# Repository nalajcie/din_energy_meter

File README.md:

# DIN Energy Meter

**this is Work In Progress, not yet stable HW/SW**

DIN Energy Meter fitting 2-unit enclosure. Features
 - 6-circuit 3-phase 
 - CT-based (external current transformers needed)
 - ESP32 as a main MCU (WiFi)
 - ATM90E32 x2 as a metering IC
 - optional display + buttons

# Hardware

TODO: 3D model of full device

For details see [Hardware README](hardware/README.md)

# Current status

## Hardware

   - **Power board** - v0.4 prototype (not assembled)
   - **Metering board** - v0.4 prototype (assembled, in test)
   - **MCU board** - breadboard prototyping

## Software
   - basic **Metering board** test with Arduino framework done

# Inspiration

This project is heavily inspired by previous work, mainly:
 - [DIN_Rail_EnergyMonitor](https://github.com/whatnick/DIN_Rail_EnergyMonitor/) by [@whatnick](https://github.com/whatnick)
 - [Expandable 6 Channel ESP32 Energy Meter](https://github.com/CircuitSetup/Expandable-6-Channel-ESP32-Energy-Meter) by [CircuitSetup](https://github.com/CircuitSetup)

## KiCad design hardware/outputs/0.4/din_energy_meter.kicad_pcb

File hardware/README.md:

# Kicad project of DIN Energy Meter

TODO: describe how to import into clean KiCad

Done in KiCad 7.0, multi-board design in hierarchical sheet. Splitting to multiple boards is done by kikit (see `split_boards.sh` for details).

# Power Board

 - Single-phase 230V AC to 3v3 DC
 - isolated 3v3 to 3v3 for power separation between ADCs and MCU
 - fliters and burden resistors for CT input
 - 2x10 2.54mm GPIO header for connecting with the **Metering Board**

# Metering Board

 - 2x ATM90E32 for energy measurement
 - CF1/2 on GPIO headers for accuracy measurement (CF3/4 on testpoints)
 - Power Manager selectors on solder jumpers
 - isolated SPI for MCU connection
 - 2x10 2.54mm GPIO header for connecting with the **Power Board**
 - 1x10 2.54mm GPIO header for connection with the **MCU board**

# MCU Board

TODO

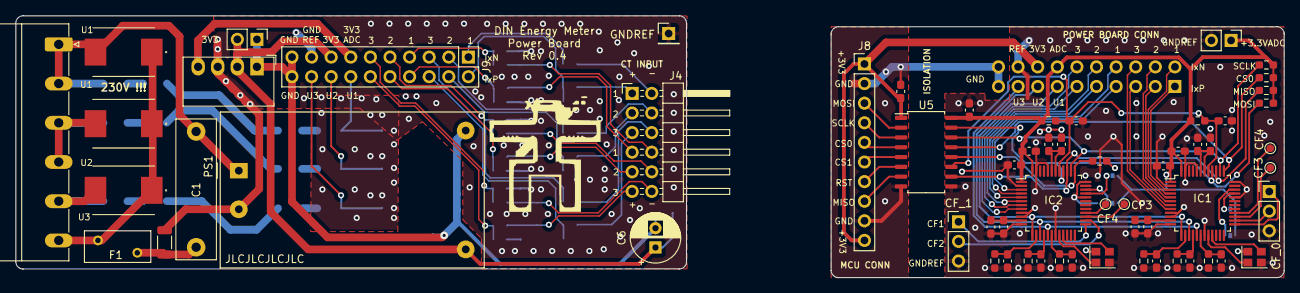
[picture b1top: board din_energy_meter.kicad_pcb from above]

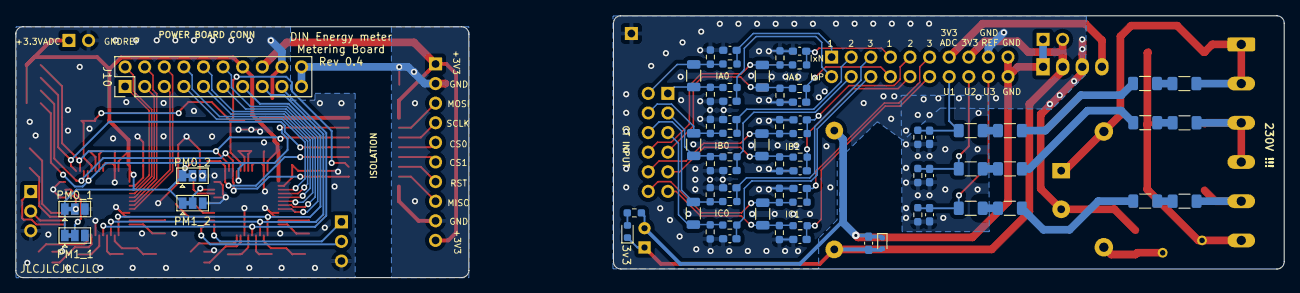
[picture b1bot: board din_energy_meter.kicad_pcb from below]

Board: 2 copper layers, 164.3 x 33.9 mm, 134 parts (69 on the bottom side), 99 nets.

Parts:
B1: PowerBoard; Board
B2: MeteringBoard; Board
C1: X2 100nF/275Vac; C_Rect_L18.0mm_W5.0mm_P15.00mm_FKS3_FKP3
C2: 1uF; C_0603_1608Metric_Pad1.08x0.95mm_HandSolder
C3, C4, C5, C10, C12, C15, C26, C28, C31, C39, C40, C41, C42, C43, C44, C45, C46, C47, C48, C49, C50: 18nF; C_0603_1608Metric_Pad1.08x0.95mm_HandSolder
C6: 100uF; CP_Radial_D6.3mm_P2.50mm
C7, C23: 4.7uF; C_0603_1608Metric_Pad1.08x0.95mm_HandSolder
C8, C9, C11, C14, C16, C17, C18, C24, C25, C27, C30, C32: 100nF; C_0603_1608Metric_Pad1.08x0.95mm_HandSolder
C13, C29: 10uF; C_0603_1608Metric_Pad1.08x0.95mm_HandSolder
D1: D_TVS; D_SOD-523
D2: 3v3; D_0603_1608Metric
F1: 120mA polyfuse; Fuse_BelFuse_0ZRE0012FF_L8.3mm_W3.8mm
G1: darwiniajack
IC1, IC2: ATM90E32AS; TQFP-48_7x7mm_P0.5mm
J1: PWR; PinHeader_1x02_P2.54mm_Vertical
J2: PHASE_CONN; PhoenixContact_MC_1,5_6-G-5.08_1x06_P5.08mm_Horizontal
J3: GNDREF; PinHeader_1x01_P2.54mm_Vertical
J4: Conn_02x06_Odd_Even; PinHeader_2x06_P2.54mm_Horizontal
J7, J11: CF_${IC}; PinHeader_1x03_P2.54mm_Vertical
J8: MCU_CONN; PinHeader_1x10_P2.54mm_Vertical
J9, J10: PowerBoard; PinHeader_2x10_P2.54mm_Vertical
J12: Conn_01x02; PinHeader_1x02_P2.54mm_Vertical
L1: 270 nH; L_1206_3216Metric
PM0_1, PM0_2, PM1_1, PM1_2: SolderJumper_3_Bridged12; SolderJumper-3_P1.3mm_Bridged12_Pad1.0x1.5mm
PS1: HLK-PM03; Converter_ACDC_HiLink_HLK-PMxx
PS2: AM1SS-0303S; Converter_DCDC_SIP4_THT
R1, R2, R3, R4, R5, R6, R7, R8, R9, R10, R11, R12: 220K; R_1206_3216Metric_Pad1.30x1.75mm_HandSolder
R13, R14, R15, R16, R17, R18, R34, R35, R36, R72, R73, R74, R75, R76, R77, R87, R88, R89, R90, R91, R92: 1K; R_0603_1608Metric_Pad0.98x0.95mm_HandSolder
R19, R37, R52, R53, R54, R55, R56: 10K; R_0603_1608Metric_Pad0.98x0.95mm_HandSolder
R22: 27; R_0603_1608Metric_Pad0.98x0.95mm_HandSolder
R63, R64, R65, R78, R79, R80: 20; R_1206_3216Metric
R66, R67, R68, R69, R70, R71, R81, R82, R83, R84, R85, R86: 2.4; R_0603_1608Metric_Pad0.98x0.95mm_HandSolder
RV1, RV2, RV3: 275 VAC; CU3225
TP2, TP11: CF3; TestPoint_Pad_D1.0mm
TP6, TP15: CF4; TestPoint_Pad_D1.0mm
U5: Π161M31; SOIC-16_4.55x10.3mm_P1.27mm
Y1, Y2: 16.384MHz; Crystal_SMD_2520-4Pin_2.5x2.0mm

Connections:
+3.3VADC: C8.2, C11.2, C18.2, C24.2, C27.2, IC1.1 (AVDD), IC1.48 (DVDD), IC2.1 (AVDD), IC2.48 (DVDD), J9.13, J10.14, J12.1, PM0_1.1 (A), PM0_2.1 (A), PM1_1.1 (A), PM1_2.1 (A), PS2.4 (+Vout), R19.1, R37.1, R52.1, R53.1, R54.1, R55.1, R56.1, U5.16 (Vdd2)
+3V3: C2.1, C6.1, C17.2, D1.2 (A2), D2.1 (K), J1.2, J8.1, J8.10, J9.15, J10.16, PS1.4 (+Vout), PS2.2 (+Vin), U5.1 (Vdd1)
/I1N_0: IC1.4 (I1N), J10.2
/I1N_1: IC2.4 (I1N), J10.8
/I1P_0: IC1.3 (I1P), J10.1
/I1P_1: IC2.3 (I1P), J10.7
/I2N_0: IC1.6 (I2N), J10.4
/I2N_1: IC2.6 (I2N), J10.10
/I2P_0: IC1.5 (I2P), J10.3
/I2P_1: IC2.5 (I2P), J10.9
/I3N_0: IC1.8 (I3N), J10.6
/I3N_1: IC2.8 (I3N), J10.12
/I3P_0: IC1.7 (I3P), J10.5
/I3P_1: IC2.7 (I3P), J10.11
/MeteringConn/CS_0: IC1.37 (~CS), R53.2, U5.13 (OUTC)
/MeteringConn/CS_1: IC2.37 (~CS), R52.2, U5.12 (OUTD)
/MeteringConn/MISO: IC1.39 (SDO), IC2.39 (SDO), R56.2, U5.10 (INF)
/MeteringConn/MOSI: IC1.40 (SDI), IC2.40 (SDI), R55.2, U5.15 (OUTA)
/MeteringConn/RESET: C16.1, C32.1, IC1.41 (~RESET), IC2.41 (~RESET), R19.2, R37.2, U5.11 (OUTE)
/MeteringConn/SCLK: IC1.38 (SCLK), IC2.38 (SCLK), R54.2, U5.14 (OUTB)
/MeteringIC0/CF1: IC1.25 (CF1), J7.1
/MeteringIC0/CF2: IC1.26 (CF2), J7.2
/MeteringIC0/PM0: IC1.33 (PM0), PM0_1.2 (C)
/MeteringIC0/PM1: IC1.34 (PM1), PM1_1.2 (C)
/MeteringIC1/CF1: IC2.25 (CF1), J11.1
/MeteringIC1/CF2: IC2.26 (CF2), J11.2
/MeteringIC1/PM0: IC2.33 (PM0), PM0_2.2 (C)
/MeteringIC1/PM1: IC2.34 (PM1), PM1_2.2 (C)
/PowerBoard/I1N_0: C40.1, J9.1, R73.1
/PowerBoard/I1N_1: C46.1, J9.7, R88.1
/PowerBoard/I1P_0: C39.1, J9.2, R72.1
/PowerBoard/I1P_1: C45.1, J9.8, R87.1
/PowerBoard/I2N_0: C42.1, J9.3, R75.1
/PowerBoard/I2N_1: C48.1, J9.9, R90.1
/PowerBoard/I2P_0: C41.1, J9.4, R74.1
/PowerBoard/I2P_1: C47.1, J9.10, R89.1
/PowerBoard/I3N_0: C44.1, J9.5, R77.1
/PowerBoard/I3N_1: C50.1, J9.11, R92.1
/PowerBoard/I3P_0: C43.1, J9.6, R76.1
/PowerBoard/I3P_1: C49.1, J9.12, R91.1
/PowerBoard/IA0+: J4.1, R63.1, R66.1, R72.2
/PowerBoard/IA0-: J4.2, R63.2, R67.2, R73.2
/PowerBoard/IA1+: J4.7, R78.1, R81.1, R87.2
/PowerBoard/IA1-: J4.8, R78.2, R82.2, R88.2
/PowerBoard/IB0+: J4.3, R64.1, R68.1, R74.2
/PowerBoard/IB0-: J4.4, R64.2, R69.2, R75.2
/PowerBoard/IB1+: J4.9, R79.1, R83.1, R89.2
/PowerBoard/IB1-: J4.10, R79.2, R84.2, R90.2
/PowerBoard/IC0+: J4.5, R65.1, R70.1, R76.2
/PowerBoard/IC0-: J4.6, R65.2, R71.2, R77.2
/PowerBoard/IC1+: J4.11, R80.1, R85.1, R91.2
/PowerBoard/IC1-: J4.12, R80.2, R86.2, R92.2
/PowerBoard/U1: C1.1, J2.1, J2.2, PS1.1 (AC/L), R1.1, RV1.2
/PowerBoard/U1_S: C3.1, J9.14, R10.2, R13.1
/PowerBoard/U1_{1}: R1.2, R4.1
/PowerBoard/U1_{2}: R4.2, R7.1
/PowerBoard/U1_{3}: R7.2, R10.1
/PowerBoard/U2: J2.3, J2.4, R2.1, RV2.2
/PowerBoard/U2_S: C4.1, J9.16, R11.2, R14.1
/PowerBoard/U2_{1}: R2.2, R5.1
/PowerBoard/U2_{2}: R5.2, R8.1
/PowerBoard/U2_{3}: R8.2, R11.1
/PowerBoard/U3: J2.5, R3.1, RV3.2
/PowerBoard/U3_S: C5.1, J9.18, R12.2, R15.1
/PowerBoard/U3_{1}: R3.2, R6.1
/PowerBoard/U3_{2}: R6.2, R9.1
/PowerBoard/U3_{3}: R9.2, R12.1
/PowerBoard/UN: F1.1, J2.6, RV1.1, RV2.1, RV3.1
/PowerBoard/UN_{in1}: C1.2, F1.2, L1.1
/U1_S: IC1.13 (V1P), IC2.13 (V1P), J10.13
/U2_S: IC1.15 (V2P), IC2.15 (V2P), J10.15
/U3_S: IC1.17 (V3P), IC2.17 (V3P), J10.17
GND: C2.2, C6.2, C17.1, D1.1 (A1), J1.1, J8.2, J8.9, J9.19, J9.20, J10.19, J10.20, PS1.3 (-Vout), PS2.1 (-Vin), R22.2, U5.8 (GND1)
GNDREF: C3.2, C4.2, C5.2, C7.1, C8.1, C9.1, C10.1, C11.1, C12.1, C13.2, C14.2, C15.1, C16.2, C18.1, C23.1, C24.1, C25.1, C26.1, C27.1, C28.1, C29.2, C30.2, C31.1, C32.2, C39.2, C40.2, C41.2, C42.2, C43.2, C44.2, C45.2, C46.2, C47.2, C48.2, C49.2, C50.2, IC1.2 (AGND), IC1.9 (IC), IC1.10 (IC), IC1.12 (AGND), IC1.19 (DGND), IC1.32 (TEST), IC1.36 (IC), IC1.44 (DGND), IC1.47 (DGND), IC2.2 (AGND), IC2.9 (IC), IC2.10 (IC), IC2.12 (AGND), IC2.19 (DGND), IC2.32 (TEST), IC2.36 (IC), IC2.44 (DGND), IC2.47 (DGND), J3.1, J7.3, J9.17, J10.18, J11.3, J12.2, L1.2, PM0_1.3 (B), PM0_2.3 (B), PM1_1.3 (B), PM1_2.3 (B), PS1.2 (AC/N), PS2.3 (-Vout), R13.2, R14.2, R15.2, R16.2, R17.2, R18.2, R34.2, R35.2, R36.2, R66.2, R67.1, R68.2, R69.1, R70.2, R71.1, R81.2, R82.1, R83.2, R84.1, R85.2, R86.1, U5.9 (GND2), Y1.2, Y1.4, Y2.2, Y2.4
unnamed: C13.1, C14.1, IC1.42 (VDD18), IC1.43 (VDD18)
unnamed: C29.1, C30.1, IC2.42 (VDD18), IC2.43 (VDD18)
unnamed: D2.2 (A), R22.1
unnamed: IC1.27 (CF3), TP2.1
unnamed: IC1.28 (CF4), TP6.1
unnamed: IC1.20 (OSCI), Y1.1
unnamed: IC1.21 (OSCO), Y1.3
unnamed: C10.2, IC1.14 (V1N), R16.1
unnamed: C12.2, IC1.16 (V2N), R17.1
unnamed: C15.2, IC1.18 (V3N), R18.1
unnamed: C7.2, C9.2, IC1.11 (VREF)
unnamed: IC2.27 (CF3), TP11.1
unnamed: IC2.28 (CF4), TP15.1
unnamed: IC2.20 (OSCI), Y2.1
unnamed: IC2.21 (OSCO), Y2.3
unnamed: C26.2, IC2.14 (V1N), R34.1
unnamed: C28.2, IC2.16 (V2N), R35.1
unnamed: C31.2, IC2.18 (V3N), R36.1
unnamed: C23.2, C25.2, IC2.11 (VREF)
unnamed: J8.3, U5.2 (INA)
unnamed: J8.4, U5.3 (INB)
unnamed: J8.5, U5.4 (INC)
unnamed: J8.6, U5.5 (IND)
unnamed: J8.7, U5.6 (INE)
unnamed: J8.8, U5.7 (OUTF)

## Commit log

2023-04-23 README: add basic readme
2023-04-23 hardware: add full kicad project
2023-04-23 hardware: add v0.4 production outputs
2023-04-23 software: add basic metering board test
    Using PlatformIO Android Framework
2023-05-01 hardware: update ibom to v0.4 release
